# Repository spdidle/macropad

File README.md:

# pommepad 🍎

## What is this?

The pommepad is an apple-shaped macropad PCB featuring 6 programmable keys, per-key RGB LEDs, and an OLED display. It's cute, it's functional, and it's shaped like an apple !! 🍎

## Why did I make this?

You know what? My fingers hurt 25/8. I spend way too long scrolling (reading, not dscrolling because heaven forbid) and doing repetitive gestures on my trackpad throughout the day, and it was starting to take a toll on my little teenage. I wanted something small that could sit next to my keyboard and handle the shortcuts and actions I use most, like pg dn & up, tab switching, clicking, or anything so my hands get a break.

I also just thought it would be fun to design a PCB that isn't a plain old rectangle, and I got inspired by my friend's apple themed airpod case. Also if you hate apples, doctors are coming after you.

## Features

- **6 mechanical key switches** — Fully programmable them :)
- **Per-key RGB LEDs** — What can I say, they're cool
- **OLED display** — Probably just to show something fun, or which app or layer I'm currently on.

## How does it work?

Each of the 6 keys can be mapped to any keystroke, shortcut, or media control you want. The OLED display will show something cute so you never want to unplug the macropad, and the per-key LEDs improve aesthetics.

## What I'm still working on

I'm going to be completely transparent with y'all, I have no idea how 3D modelling works. You know how they say "Blender is the only program where beginners impress the pros,"? I feel like there should be a saying for Fusion 360 as well. Everything on that app makes me feel like a newborn baby in a cockpit. I don't know what I'm doing at all, evidently, so this project might actually be halted until I find motivation and courage to open Fusion again.

Part of it comes from my PCB being really oddly shaped that I don't even know where to start. The tutorials online only feature rectangular or square shaped PCBs so having an apple is definitely... a very "smart" choice that I made.

Unless someone would be open to teaching me... and I wouldn't be oppposed to that at all...

## Design

Designed in KiCad, schematic and board files are in this repo! There is also a firmware test but do NOT rely on it whatsoever. (not like this project is getting touched anytime soon)

Case will be (soon) designed in Fusion 360!

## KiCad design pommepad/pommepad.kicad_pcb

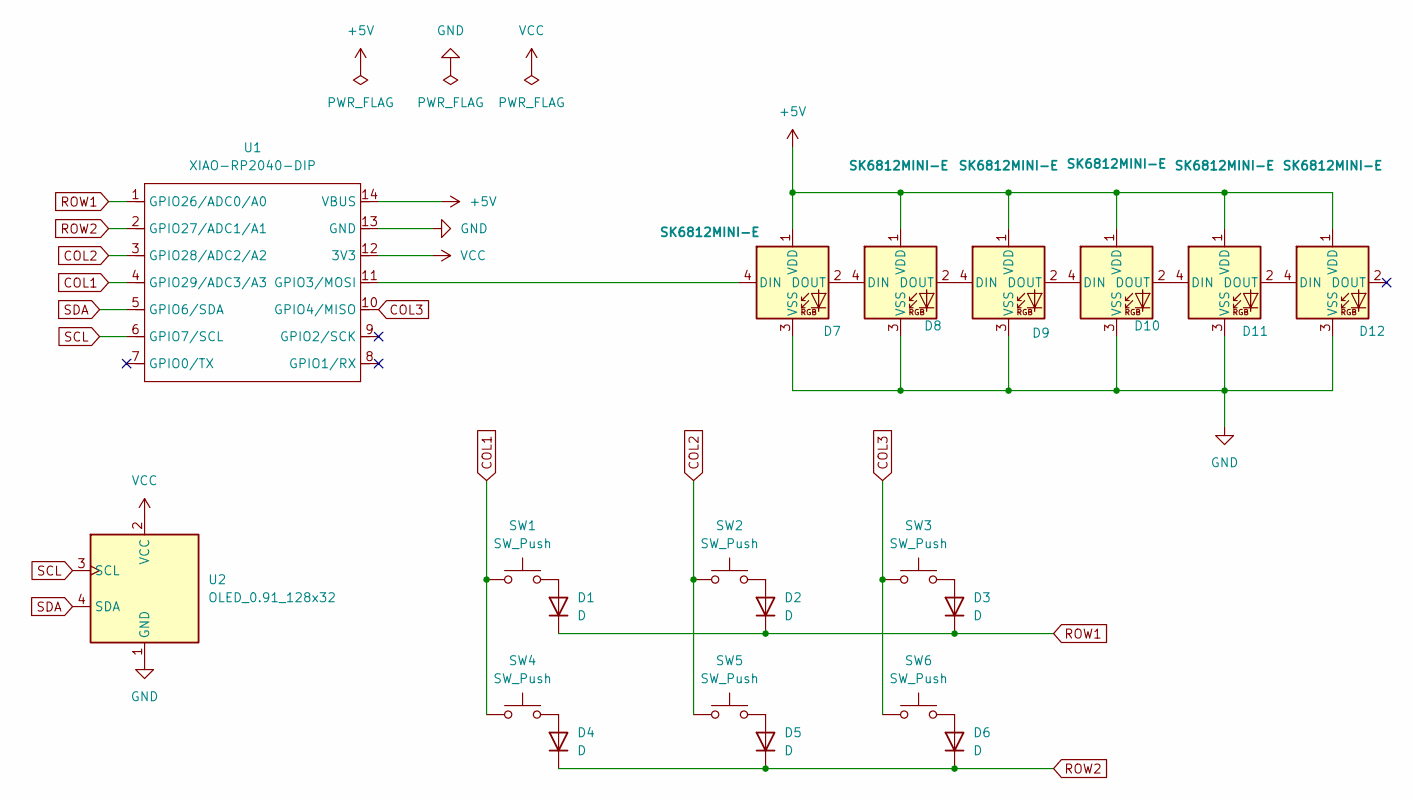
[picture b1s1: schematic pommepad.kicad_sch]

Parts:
D1, D2, D3, D4, D5, D6: D; D_DO-35_SOD27_P7.62mm_Horizontal
D7, D8, D9, D10, D11, D12: SK6812MINI-E; SK6812MINI-E_fixed
SW1, SW2, SW3, SW4, SW5, SW6: SW_Push; SW_Cherry_MX_1.00u_PCB
U1: XIAO-RP2040-DIP
U2: OLED_0.91_128x32

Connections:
5V: D7.1 (VDD), D8.1 (VDD), D9.1 (VDD), D10.1 (VDD), D11.1 (VDD), D12.1 (VDD), U1.14 (VBUS)
COL1: SW1.1, SW4.1, U1.4 (GPIO29/ADC3/A3)
COL2: SW2.1, SW5.1, U1.3 (GPIO28/ADC2/A2)
COL3: SW3.1, SW6.1, U1.10 (GPIO4/MISO)
GND: D7.3 (VSS), D8.3 (VSS), D9.3 (VSS), D10.3 (VSS), D11.3 (VSS), D12.3 (VSS), U1.13 (GND), U2.1 (GND)
unnamed: D1.2 (A), SW1.2
unnamed: D2.2 (A), SW2.2
unnamed: D3.2 (A), SW3.2
unnamed: D4.2 (A), SW4.2
unnamed: D5.2 (A), SW5.2
unnamed: D6.2 (A), SW6.2
unnamed: D7.4 (DIN), U1.11 (GPIO3/MOSI)
unnamed: D7.2 (DOUT), D8.4 (DIN)
unnamed: D8.2 (DOUT), D9.4 (DIN)
unnamed: D9.2 (DOUT), D10.4 (DIN)
unnamed: D10.2 (DOUT), D11.4 (DIN)
unnamed: D11.2 (DOUT), D12.4 (DIN)
ROW1: D1.1 (K), D2.1 (K), D3.1 (K), U1.1 (GPIO26/ADC0/A0)
ROW2: D4.1 (K), D5.1 (K), D6.1 (K), U1.2 (GPIO27/ADC1/A1)
SCL: U1.6 (GPIO7/SCL), U2.3 (SCL)
SDA: U1.5 (GPIO6/SDA), U2.4 (SDA)
VCC: U1.12 (3V3), U2.2 (VCC)

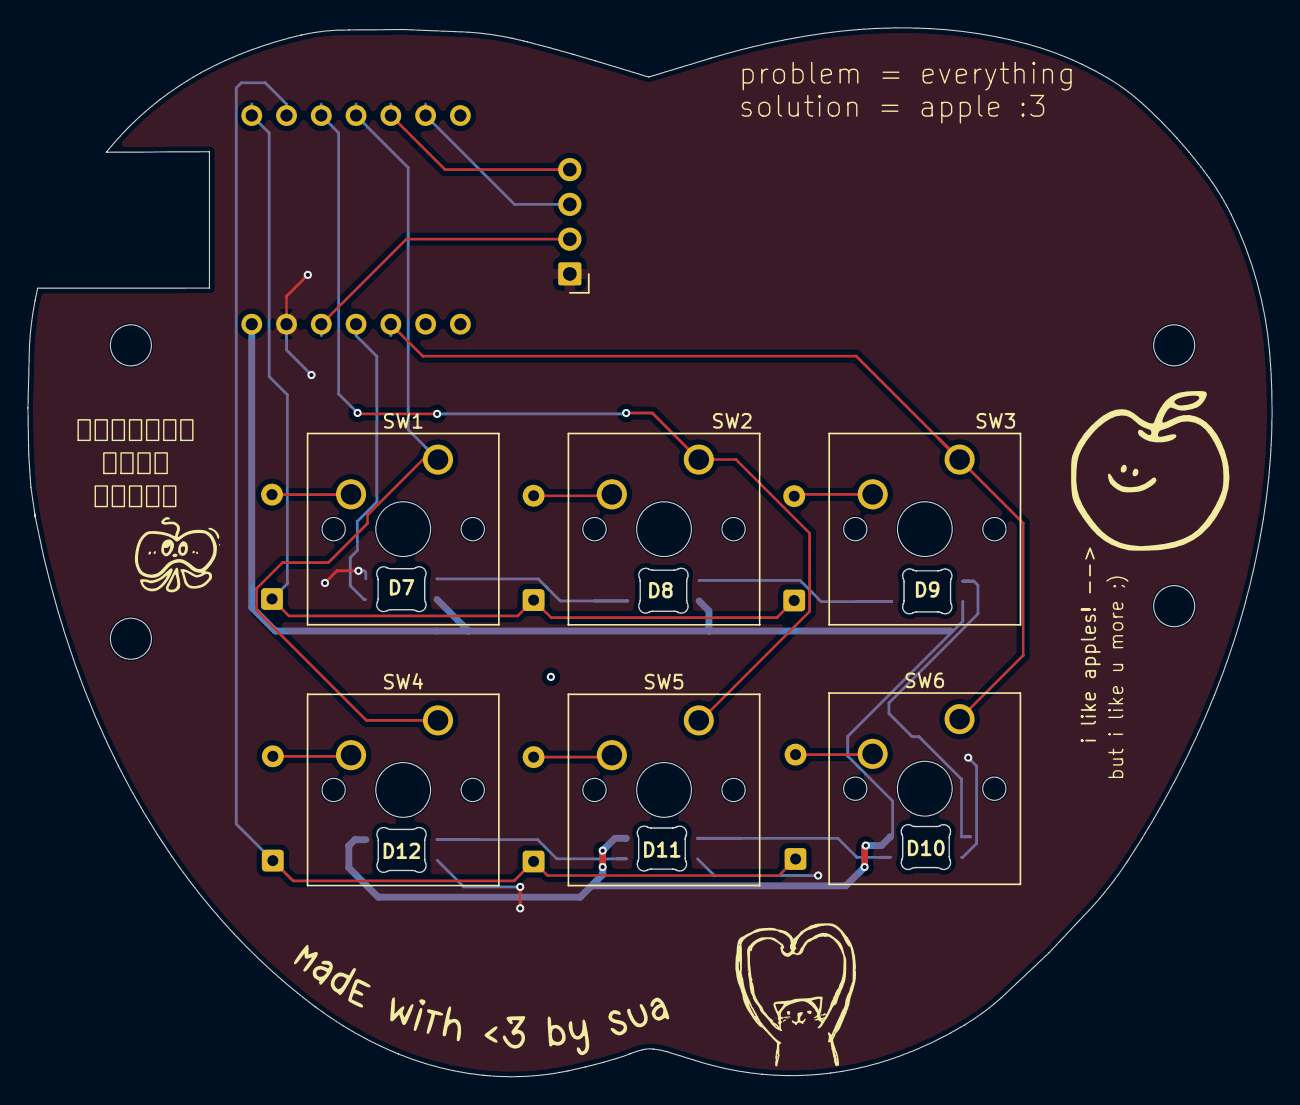
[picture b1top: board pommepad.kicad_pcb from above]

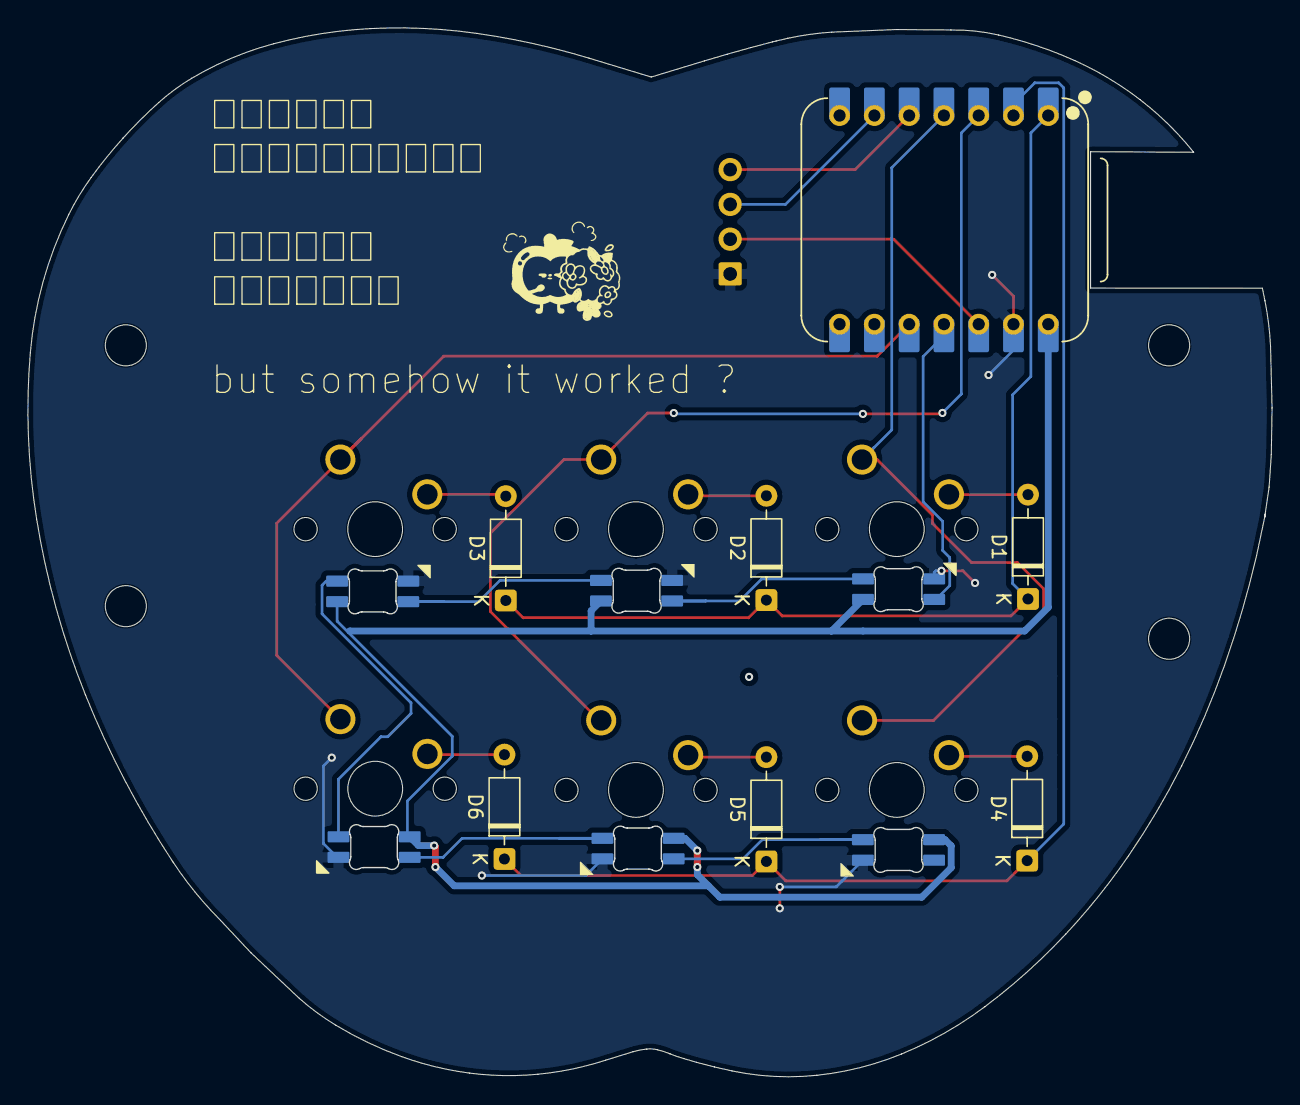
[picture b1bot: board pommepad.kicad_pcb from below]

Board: 2 copper layers, 90.9 x 76.6 mm, 20 parts (7 on the bottom side), 22 nets.

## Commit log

2026-03-18 work
2026-03-18 dxfcgvhbjn
2026-03-19 fix
    deleted my whole folder mb
2026-03-23 Revise README
    updated my readme bois we are READY to ship 😂😂😂🫱
2026-03-23 update readmie
    nvm NOW we're ready to ship
2026-03-23 added firmware test
    dont laugh ik it sucks i wrote it relly fast its just so i can ship it 😔
2026-04-03 hourly commit
    no reason :)
2026-04-04 WHAT THE HELL. (restore)
    I DONT KNOW WHAT JUST HAPPENED OH MY BABY ILL NEVER TAKE YOU FOR GRANTED EVER AGAIN cuz wth did i even do last night? how did my entire project get deleted im so confused but its ok. we're so bad (i 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
2026-04-19 war is over.
    I FINISHED THE PCB IM IN TEARS BRO
2026-04-19 wait hello
    i didnt know a bunch of filles changed so ig ill just commit but uhh know that i didnt change anythign ig ?
2026-04-19 commituy
    fix readmee with a new pic of the pcb, and ummmm updated some stuff idk
